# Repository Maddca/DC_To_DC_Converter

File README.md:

# Portable Battery Phone Charger
This project was done in collaboration with [Taylor Smith](https://github.com/TaylorSmith28).
## Overview
This is a Portable Battery based Phone Charger Design for Walla Walla University's Power Electronics Course. The goal of this project was to create a 12-15V to 5V DC converter in order to be able to charge a phone from a voltage source ranging from 12-15V.
## Design Specifications
1. Takes a 12-15V input and outputs a 5V
2. Is able to charge both Android Devices as well as Iphones
3. Able to handle any 12-15V source that might be used. (Up to 3A)
4. Power efficiency of atleast 80%
5. Small Board Size (less than 10cm x 10cm)
6. Costs less than $25

## Block Diagram

## Schematic

### Buck Converter

Shown above is the final schematic for our project. Our input is delived from a 12-15V source to the screw terminal. For our final version we used a set of 8 AA batteries to generate 12V into the screw terminal. The input then passes a ferrite bead in order to limit noise coming from the input. It then passes into a LM25765-5 Buck Converter. The LM25765 works as a simple switcher in conjuction with our inductor and schottky diode in order to create an average duty cyle resulting in 5V. From the USB 5V are generated with a current ranging from about 20-30mA. This is entirely dependent on what kind of battery you use. The converter itself is designed to handle up to 3A so you are able to charge your phone with a car battery.

### Data Pin Voltage Divider

5V is passed into a voltage divider, in order to use the data pins on the USB output. This is required to charge Apple Devices. We got the required Data Pin Voltages from https://blog.voltaicsystems.com/choosing-usb-pin-voltages-for-iphones-and-ipads/.

## PCB Design

Shown above is the lastest PCB design. Of interest is the particularly wide track width, which is required because of our design specification of being able to handle at least 3A. Besides that parts, besides the voltage divider for the data pins, have been picked to handle no less than 3A.

## Simulations

Above is the DC simulation showing the duty cycle. This was done through Webenches internal simulator.
[WEBENCH](https://www.ti.com/design-resources/design-tools-simulation/webench-power-designer.html)
## Results

The final results were that as expected the device can charge any type of phone including iphones. It has a power efficiency of more than 80%. It can supply up to 3A, but the capacitors in particular get hot rather quickly so don't leave it plugged in for very long. The low current diplayed(20-30mA)in the previous image was likely due to the AA batteries being used to charge a phone for several hours of total charging times previous to the image being taken.

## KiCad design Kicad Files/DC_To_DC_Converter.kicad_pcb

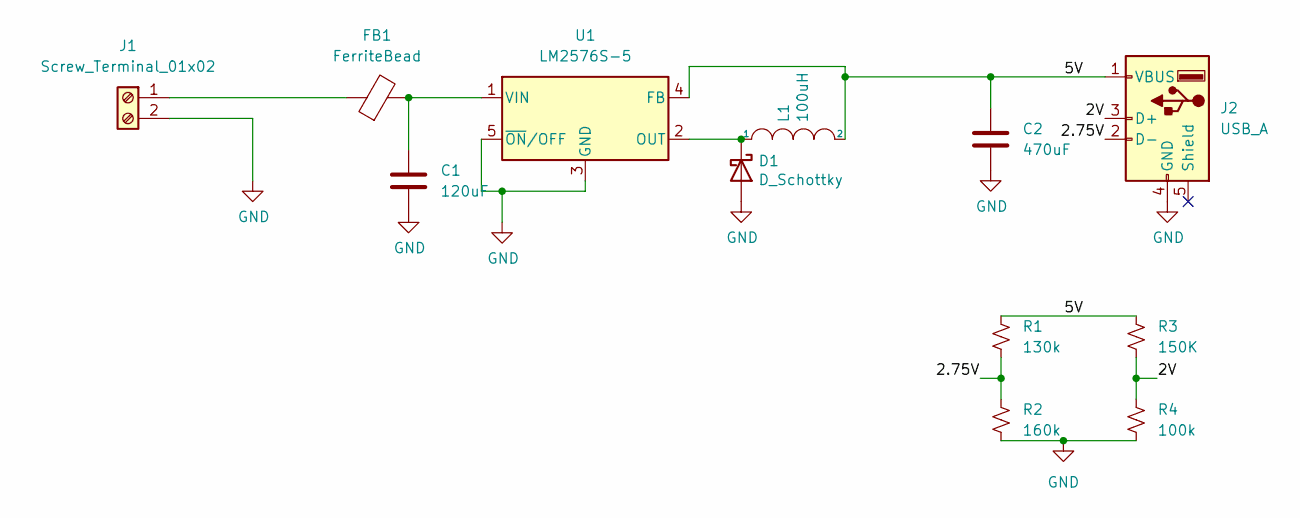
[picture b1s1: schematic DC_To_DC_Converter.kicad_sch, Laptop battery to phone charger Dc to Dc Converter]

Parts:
C1: 120uF; CP_Radial_D8.0mm_P3.50mm
C2: 470uF; CP_Radial_D8.0mm_P3.50mm
D1: D_Schottky; D_DO-15_P15.24mm_Horizontal
FB1: FerriteBead; LairdTech_28C0236-0JW-10
J1: Screw_Terminal_01x02; 2 Pin TB006-508 Terminal Block
J2: USB_A; USB_A_Molex_67643_Horizontal
L1: 100uH; L_28x25mm_H20.5mm
R1: 130k; R_0805_2012Metric
R2: 160k; R_0805_2012Metric
R3: 150K; R_0805_2012Metric
R4: 100k; R_0805_2012Metric
U1: LM2576S-5; TO-263-5_TabPin3

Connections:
/2.75V: J2.2 (D-), R1.2, R2.1
/2V: J2.3 (D+), R3.2, R4.1
/5V: C2.1, J2.1 (VBUS), L1.2, R1.1, R3.1, U1.4 (FB)
GND: C1.2, C2.2, D1.2 (A), J1.2, J2.4 (GND), R2.2, R4.2, U1.3 (GND), U1.5 (~ON/OFF)
unnamed: C1.1, FB1.2, U1.1 (VIN)
unnamed: D1.1 (K), L1.1, U1.2 (OUT)
unnamed: FB1.1, J1.1

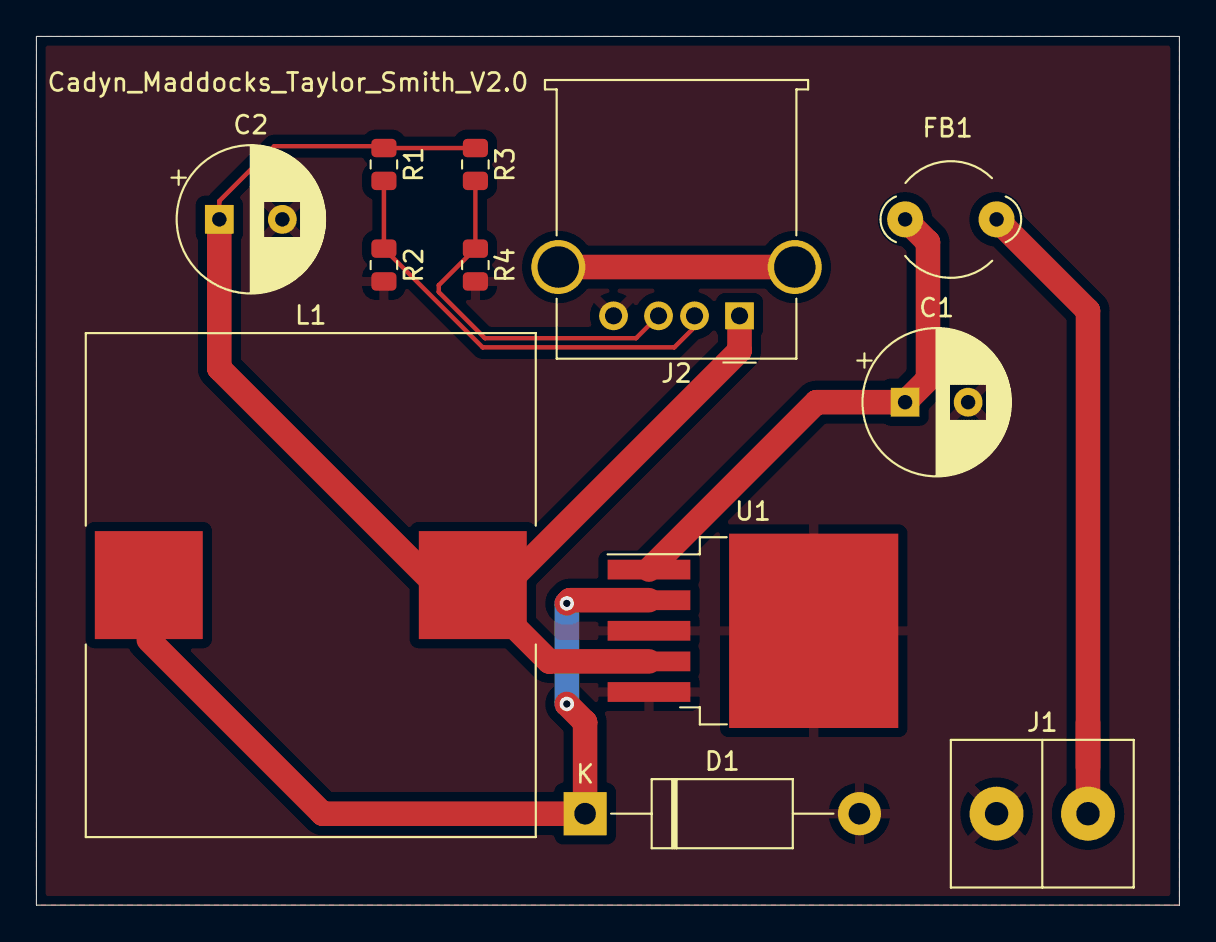
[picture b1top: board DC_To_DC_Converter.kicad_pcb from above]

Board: 2 copper layers, 63.5 x 48.3 mm, 12 parts (0 on the bottom side), 7 nets.

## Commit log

2022-06-08 Uploading Files
2022-06-08 Added Simulation Images
2022-06-08 Added images of the results
2022-06-08 Fixed Problem on the schematic
2022-06-08 Changed images
